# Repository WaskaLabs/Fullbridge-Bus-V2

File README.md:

# Fullbridge-Bus-V2
The full-bridge bus 2.0 is a fully integrated "high side" system designed for SSTC, DRSSTC Tesla coils, and other high power inverter applications.

PCB and Kits available for sale in the WaskaLabs store on tindie.com

Finished System Specs:

- Works with 110 and 220 AC voltages (requires relevant components for voltage!)
- High current design capable of ~300+ Apk
- Low stray inductance bridge design
- TO-247 MOSFETs or IGBTs - Surface mounted for easy and fast replacement
- Direct mount to large 100mm X 120mm heatsink for maximum temperature handling
- 10A RMS bridge rectifier and bus capacitors (voltage doubler configuration, can be set up as standard rectified) with high current input for mains AC or variac AC voltage.
- Safety circuits (6x20mm fuse (Comes with fast-blow 10A), bus capacitor bleeder resistor)
- Gate drive components (Series resistor, antiparallel switch-off diode, TVS diode) and marked solder pads for easy GDT connection.
- Snubber capacitors (0.66uF total)
- Optional diodes (freewheel or TVS on inverter output)
- High current screw connectors used (All metal)
- Optional MMC and CT board for all-in-one DRSSTC system (Coming soon)

Comes with:

- PCB
- SMD components (pre-soldered)
- Connectors (pre-soldered)
- Bridge rectifier (pre-soldered)
- Bleeder resistor (pre-soldered)
- Fuse holder and 10A fast-blow fuse (pre-soldered)
- 4x silicone heat pads
- Printed hole placement guide

Required - Not included in kit:

- Bus capacitors (~$8 each eBay, Amazon) (Choose appropriate voltage for your country)
- IGBTs or MOSFETs (Mouser, Digikey) (Spec for your specific design)
- 100x120mm Heatsink ($10 on Amazon)
- M3 screws and nylon standoffs
- GDT (DIY or available as an addon)

IGBT and MOSFET recommendations:

- FGA60N65SMD (Best in my experience) (Great for DRSSTC)
- FGA60N60SMD (Similar to 60N65) (Great for DRSSTC)
- IRFP460 (Great for higher frequency, low current SSTC designs)

Rectifier & Bus:

The voltage doubler configuration doubles the peak-to-peak voltages seen on the AC input. For example, US mains is 110V RMS, but ~170Vpp. So if US mains is connected directly to the input, it should charge the capacitor bank to 2 x 170V (~340V). The capacitors on the bus are connected in series, so each capacitor should be rated to hold the full Vpp of the mains input (in the US, I like to use 250V). It is highly advisable to spec these caps to handle >30% more than the voltage you expect to see in them, so a 500V total cap charged to 340V is a safe bet. In 220V land, you will want to use 450V capacitors for a total of 900V. Bare in mind that the total capacitance of the bus will decrease by half as the voltage doubles. So two 250V 1000uF caps in series will give you 500V at 500uF. This should be kept in consideration when designing the system.

Recommendations:

- US mains (110V RMS) - 250V 1000uF capacitors (10mm lead spacing, 35mm dia max)
- International mains (220V RMS) - 450V 680 - 1000uF capacitors (10mm lead spacing, 35mm dia max)

If you plan to modify the board to a standard rectified voltage, spec your caps accordingly. I would suggest ~100V caps for US mains (200V total rating), doubling it for 220V mains, at the highest uF you can get in the correct footprint to fit the PCB.

The KBU-1010 bridge rectifier is rated for 10A continuous and 300A surge. If you plan to run high currents monitor the temperature of the rectifier and add a heatsink if needed. The fuse is a 6x20 cylindrical type and are standard and available cheap online or locally at hardware stores. 

Inverter & Gates:

The inverter portion is pretty straightforward. The switches (IGBTs or MOSFETs) are connected directly to the heatsink with a silicone heat pad (sil pad) to electrically isolate the switches from the heatsink (Very important!). The pins of the switches should be bent upwards before mounting, then bent to contact the pads and soldered in place. Removal can be done with a soldering iron, but the simple solution is to use hot air to heat the pads. It is easier to do this after unscrewing the switches from the heatsink, otherwise you may not be able to disconnect it easily. The leads can also be clipped first if this becomes an issue.

The Gate Drive Transformer (GDT, typically 1:1:1:1:1) should be wound and phased. The secondary windings of the GDT should be soldered directly to the pads with the phase wires soldered to the pads with silkscreen around them, and the anti-phase ends soldered to the other pad. Make sure to wind the GDT with enough extra wire to make it easy to mount (I like to mount them to the side of the heatsink). One important note is that the GDT secondaries should ALL BE LENGTH MATCHED to avoid skew in the timing between the switches. 

The gate components are not one size fits all. The gates and waveforms should be thoroughly tested to assure the switching waveform is correct. If it isn't, you may need to change gate resistors and remove the diodes, etc. until you can get it right. The TVS diodes are SMAJ26 26V TVS which is designed for up to 24V drive voltages. If using lower voltages you may want to change the value of the TVS. Tuning gates is not in the scope of this document, but it is an art and takes some time to get right. But having a proper driver, GDT, gate components, and the right switches are important in getting this right. A good resource for this is Ritchie Burnett's GDT waveform troubleshooting guide.

Step by Step Assembly:

1. Spec and purchase all components for your design. Refer to BOM.
2. Solder bus caps onto PCB and test the DC voltage across the bus as well as voltage drain from bleeder resistor (recommended through a variac!).
3. Drill and tap all M3 holes in the PCB (Use printable guide). Aluminum is soft, so be careful here! If you accidentally strip the holes, you can run a longer screw all the way through and a nut on the back of the heatsink.
4. Screw down TO-247 IGBT switches with a sil pad to keep it electrically separated from the heatsink. I like to use thermal paste on both sides of the silpad for added thermal conduction. Make sure to bend the pins upwards so the PCB fits in between them.
5. Mount the PCB to the heatsink using standoffs (3 - 5mm is usually fine). Make sure the PCB connections and solder points do NOT and will NOT touch the heatsink!!
6. Bend the IGBT switch leads down to the pads and solder them in place.
7. Mount the GDT and solder the wires to the gate drive pads. Ensure correct phasing.

Testing Gates:

1. Connect a proper driver to the GDT primary and drive the gates at a frequency as close as possible to your desired operation frequency (Function generator to the GDT driver works well)
2. Test the Gates:
	1. Probe the gate drive signal to assure gate waveforms look good using an oscilloscope.
	2. Change out components or circuit elements as needed to get a good gate drive waveform. Not always needed.
	3. Assure all gates look good before proceeding...

Testing Inverter:

1. Make sure you are interrupting the output or have a high enough impedance to not drain your capacitors. This is design dependant, but should be done for any SSTC/DRSSTC design
2. Connect the load to the inverter output (Primary coil you plan to drive or high Z load for low voltage testing) (NO SECONDAY IF SSTC/DRSSTC)
3. Connect a variac and set the DC bus voltage to a low test voltage (~20-50V)
4. Hook up an oscilloscope between D/S leads on one of the switches and test the waveform. Do this with all switches. Assure they are all switching properly before proceeding.
5. Now test the output of the inverter. Be sure you are seeing a proper square wave. If you see a stair step pattern, one of the switches may be phased wrong. You may see droop in the center of the square wave depending on your load. Careful with MMCs here is using DRSSTCs. You wont be driving at resonance so this may give you a weird output. Try removing it if it causes issues.
6. Now you can increase the voltage and watch the waveforms on the scope to assure it is working as expected.

Troubleshooting:

- Make sure all gates are phased properly and being driven in the correct direction
- Test different gate drive components and values
- Make sure none of the switches are bad. Rare but it happens. If the bridge blows, all the switches may need to be replaced even if some seem okay
- Make sure you are providing enough drive current to the GDT
- Make sure your load has enough impedance to not just drain the caps too fast to see inverting voltages

This design is meant to be configurable and modular to be able to fit many topologies. There are far too many variations in application, drive methods, and use cases for me to be able to help in the debugging. If you have issues getting it to work, do your research and read up on forums. I have provided schematics and resource information on the system so that you have all information necessary to figure out the issue. But standard troubleshooting like adding/removing components and thinking through the design will be the only way to get it running. I am happy to help when I can, but ultimately what you build with this cannot be fixed IT style.

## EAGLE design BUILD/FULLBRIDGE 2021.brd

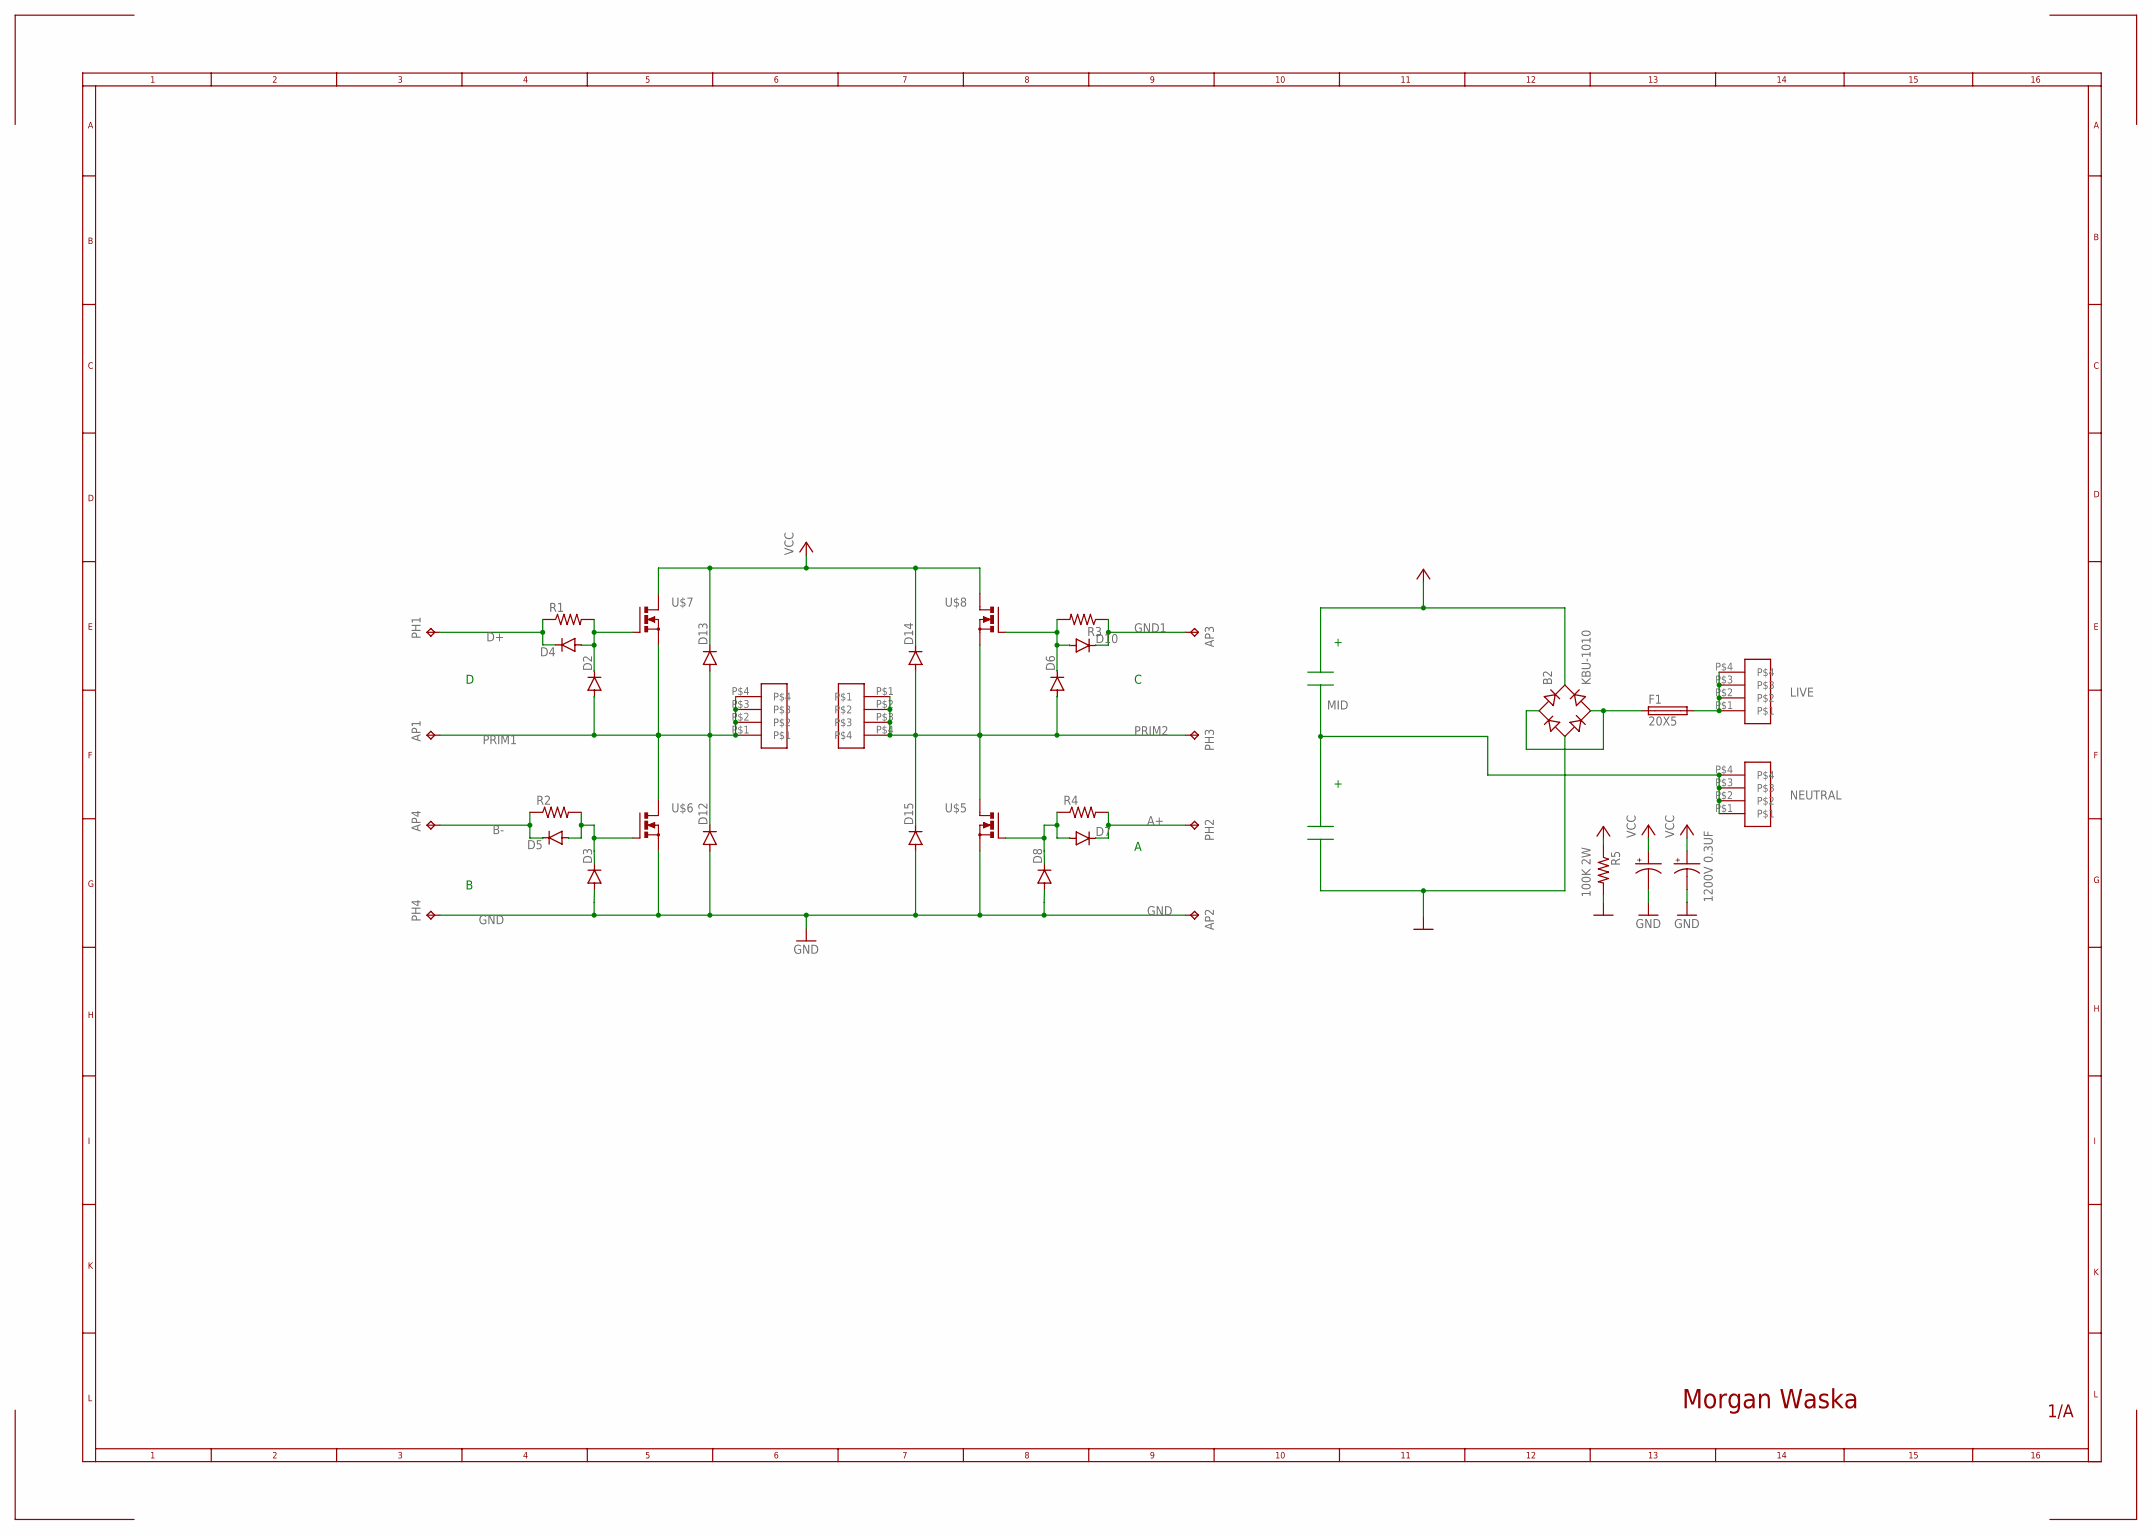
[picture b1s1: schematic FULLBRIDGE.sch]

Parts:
AP1, AP2, AP3, AP4: TPTP20SQ; TP20SQ
B2: KBU-1010; KBU
D2, D3, D6, D8: SMAJ26CA; DO214AC
D4, D5, D7, D10: SS14-E3/5AT; DO214AC
D12, D13, D14, D15: 440V TVS; DO15-12
F1: 20X5; GSH15
LIVE: KEY7788; 7788
NEUTRAL: KEY7788; 7788
PH1, PH2, PH3, PH4: TPTP20SQ; TP20SQ
R1, R2, R3, R4: R-US_M1206; M1206
R5: 100K 2W; 0411/12
U$1, U$2: KEY7788; 7788
U$3, U$4: CHINEMKP; CHINESEMKP
U$5, U$6, U$7, U$8: FGA60N65SMD_SMD; TO247BH

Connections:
A+: D7.C, PH2.TP, R4.2
B-: AP4.TP, D5.C, R2.1
D+: D4.C, PH1.TP, R1.1
GND: AP2.TP, B2.-, D3.A, D8.A, D12.A, D15.A, PH4.TP, R5.2, U$3.P$2 (-), U$4.P$2 (-), U$5.S, U$6.S
GND1: AP3.TP, D10.C, R3.1
MID: NEUTRAL.P$1, NEUTRAL.P$2, NEUTRAL.P$3, NEUTRAL.P$4
unnamed: F1.2, LIVE.P$1, LIVE.P$2, LIVE.P$3, LIVE.P$4
unnamed: D6.C, D10.A, R3.2, U$8.G
unnamed: B2.AC1, B2.AC2, F1.1
unnamed: D3.C, D5.A, R2.2, U$6.G
unnamed: D2.C, D4.A, R1.2, U$7.G
unnamed: D7.A, D8.C, R4.1, U$5.G
PRIM1: AP1.TP, D2.A, D12.C, D13.A, U$1.P$1, U$1.P$2, U$1.P$3, U$1.P$4, U$6.D, U$7.S
PRIM2: D6.A, D14.A, D15.C, PH3.TP, U$2.P$1, U$2.P$2, U$2.P$3, U$2.P$4, U$5.D, U$8.S
VCC: B2.+, D13.C, D14.C, R5.1, U$3.P$1 (+), U$4.P$1 (+), U$7.D, U$8.D

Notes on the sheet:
Morgan Waska
1/A
LIVE
NEUTRAL
1200V 0.3UF

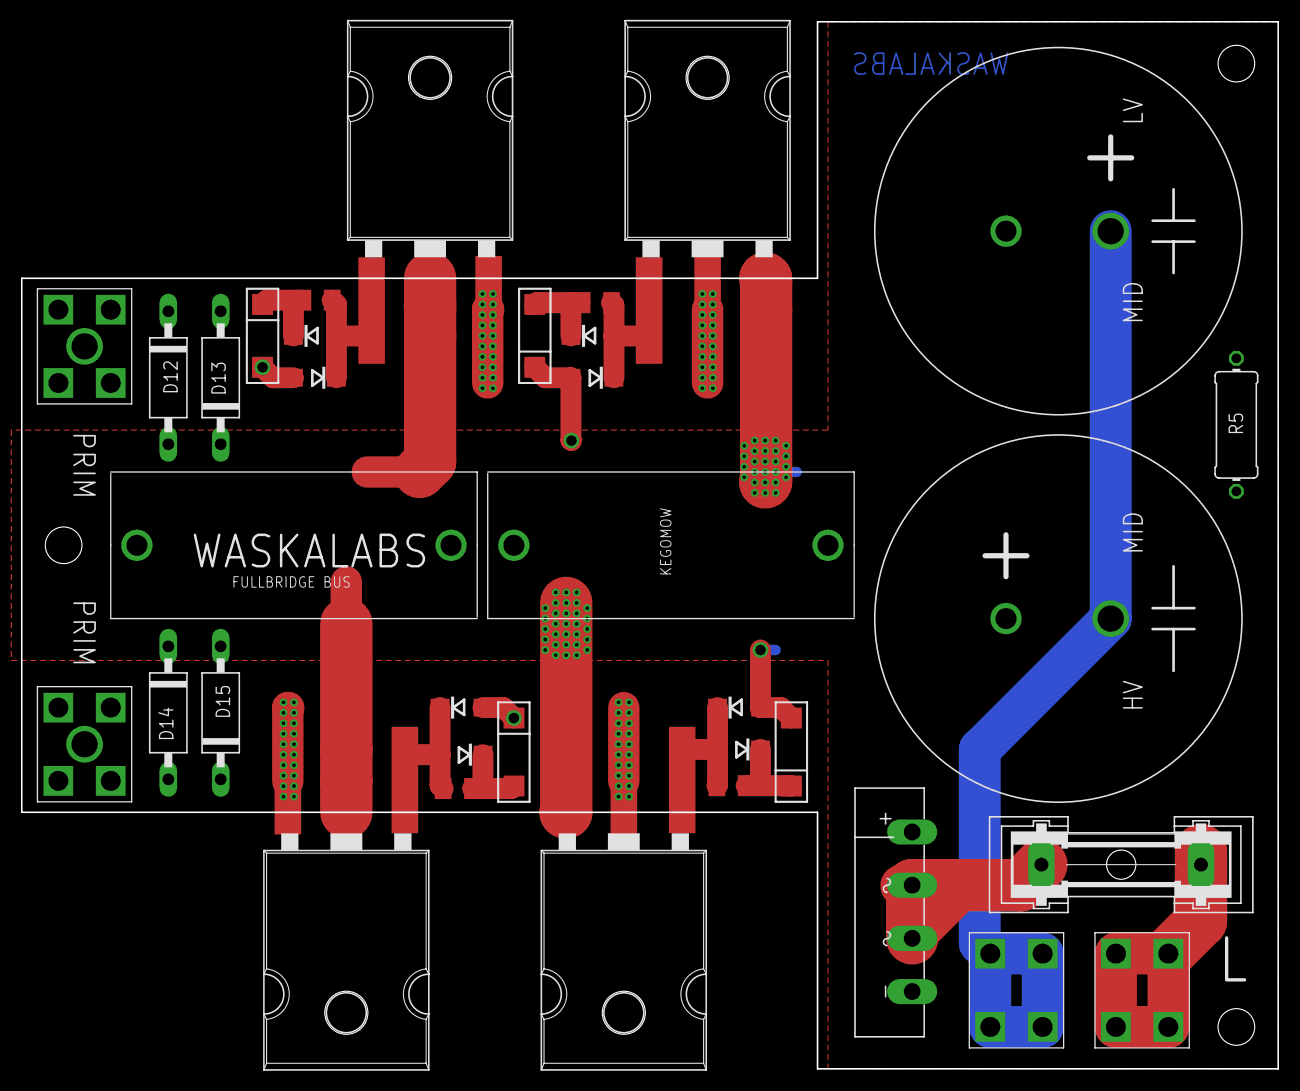
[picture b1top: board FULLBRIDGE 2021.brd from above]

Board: 2 copper layers, 120.0 x 100.0 mm, 37 parts (0 on the bottom side), 15 nets.
